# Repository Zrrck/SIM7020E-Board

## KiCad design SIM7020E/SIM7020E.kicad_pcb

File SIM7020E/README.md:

# SIM7020E-Board
I am designing SIM7020E board using STM32.

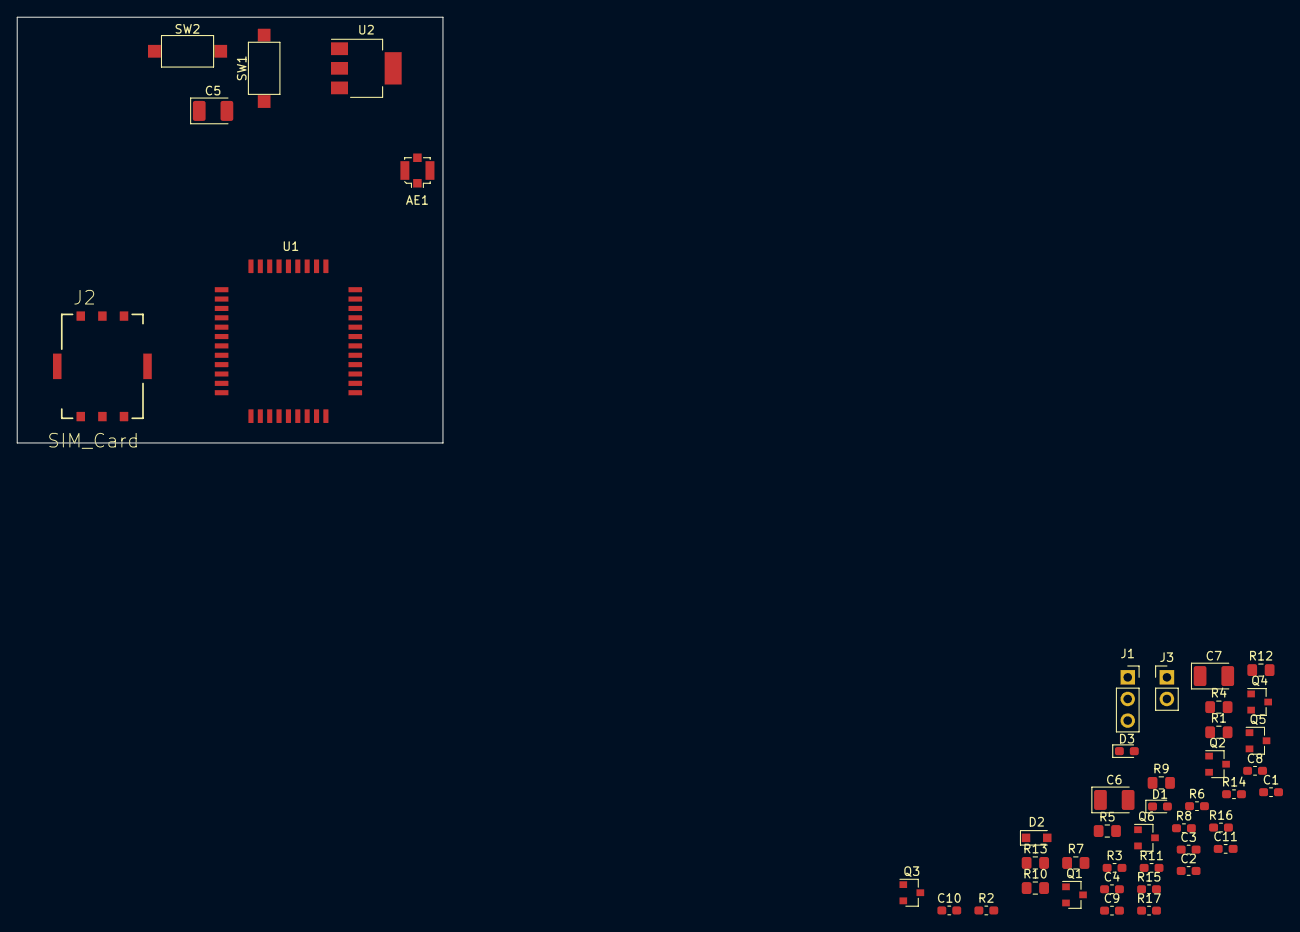
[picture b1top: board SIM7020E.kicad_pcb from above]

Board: 2 copper layers, 50.0 x 50.0 mm, 45 parts (0 on the bottom side), 28 nets, no tracks yet.

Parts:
AE1: Antenna; U.FL_Molex_MCRF_73412-0110_Vertical
C1, C2, C4, C11: 100nF; C_0603_1608Metric_Pad1.05x0.95mm_HandSolder
C3: 1uF; C_0603_1608Metric_Pad1.05x0.95mm_HandSolder
C5, C6, C7: 100uF; CP_EIA-3528-21_Kemet-B_Pad1.50x2.35mm_HandSolder
C8, C9, C10: 22pF; C_0603_1608Metric_Pad1.05x0.95mm_HandSolder
D1, D3: LED; LED_0603_1608Metric_Pad1.05x0.95mm_HandSolder
D2: 5.1 V 500 mW; D_SOD-323_HandSoldering
J1: Conn_01x03; PinSocket_1x03_P2.54mm_Vertical
J2: SIM_Card; GCT_SIM8051-6-0-14-00-X-REVD
J3: Conn_01x02; PinHeader_1x02_P2.54mm_Vertical
Q1, Q2, Q3, Q4, Q5, Q6: Q_NPN_BCE; SOT-23
R1, R4, R5, R7, R9, R10, R12, R13: 4.7K; R_0805_2012Metric_Pad1.15x1.40mm_HandSolder
R2, R3, R6, R8, R11, R14: 47K; R_0603_1608Metric_Pad1.05x0.95mm_HandSolder
R15, R17: 22 ohm; R_0603_1608Metric_Pad1.05x0.95mm_HandSolder
R16: 22ohm; R_0603_1608Metric_Pad1.05x0.95mm_HandSolder
SW1, SW2: SW_Push; SW_SPST_CK_RS282G05A3
U1: SIM7020E
U2: AMS1117-3.3; SOT-223-3_TabPin2

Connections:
GND: C1.2, C2.2, C3.2, C4.2, C5.2, C6.2, C7.2, C8.1, C9.2, C10.1, C11.1, D2.2, J1.3, J3.2, Q1.3, Q3.3, Q5.3, Q6.3, R2.2, R6.1, R11.2, R14.1, U1.36, U2.1
NETLIGHT: R13.1, U1.41
unnamed: AE1.1, U1.32
unnamed: C8.2, R15.2, U1.15
unnamed: C9.1, R17.2, U1.17
unnamed: C10.2, R16.2, U1.16
unnamed: D1.1, Q3.2
unnamed: D3.1, Q6.2
unnamed: Q1.1, R1.2, R2.1
unnamed: Q2.1, R3.1, R5.2
unnamed: Q3.1, R4.2, R6.2
unnamed: Q4.1, R9.2
unnamed: Q5.1, R10.2, R11.1
unnamed: Q6.1, R13.2, R14.2
unnamed: R1.1, SW1.2
unnamed: R10.1, SW2.2
PWRKEY: C1.1, Q1.2, U1.39
RESET: C2.1, Q5.2, U1.28
RX: J1.2, Q2.2, R7.2
SIM_VDD: C11.2, U1.18
STATUS: R4.1, U1.42
TX: J1.1, Q4.3, R8.2
UART1_RXD: Q4.2, R12.2, U1.2
UART1_TXD: Q2.3, R3.2, U1.1
UART_VDD: R7.1, R8.1
VBAT: C3.1, C4.1, C5.1, C6.1, C7.1, D1.2, D2.1, D3.2, SW1.1, SW2.1, U1.34, U2.2
VDD_EXT: R5.1, R9.1, R12.1, U1.40
VIN: J3.1, U2.3

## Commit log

2019-09-13 Basic pcb setup
2019-09-14 Create LICENSE
2019-09-28 shematic update
2019-09-28 pcb update
